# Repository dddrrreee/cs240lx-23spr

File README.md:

## CS240lx: advanced operating system lab, accelerated
### Engler, Spr 2023.

tl;dr index:

  - [This is a lab class and here are the labs](./labs/).
  - [Course website](https://github.com/dddrrreee/cs240lx-23spr).
  - [Course newsgroup](https://github.com/dddrrreee/cs240lx-23spr).
  - To get the repository: 

        git clone git@github.com:dddrrreee/cs240lx-23spr.git

    Put the path to the repo in your shell startup file:

    E.g. for `tcsh` I put the following in my `.tcshrc` file (and
    did `source ~/.tcshrc` after):
 
        setenv CS240LX_2023_PATH /home/engler/class/cs240lx-23spr/

    If these steps worked, you should be able to type `make` and have
    it work.

This is a implementation-heavy, lab-based class that will cover similar
topics as CS240 --- threads, virtual memory, file systems and distributed
systems --- but by writing code versus discussing papers.  After taking an
initial operating systems course you are often left in the odd situation
of having spent significant time getting the background knowledge needed
to do interesting actions, but not being left with enough time to actually
do them.  This course attacks this problem by assuming basic knowledge and
using it as a springboard to advance quickly through a set of powerful,
useful techniques that even advanced practioners can be ignorant of.

We will write custom code from scratch for the widely-used, ARM-based
raspberry pi; our code will run "bare-metal" without an operating system,
which means we can do interesting things without constantly fighting
with a lumbering OS that cannot get out of its own way.

By combining research insights (many unpublished) and our our lightweight
bare-metal code we will be in the unusual position of having foundational
abilities that most people have assumed are in-practice impossible.
As one example, we will implement fast, flexible exception handling
and then use this ability to build a variety of tools that find race
conditions, check code correctness, and memory  corruption.  By using
exceptions rather than binary rewriting we can build tools that find
similar errors as Purify / Valgrind, but can be implemented in merely
hundreds rather than hundreds of thousands of lines of code; our tools
will also be faster and more extensible.

Our initial plan was to do ten projects, one per week, where each project
covers two labs of (at a minimum) several hours each and a non-trivial
amount of outside work.

The course workload is significant, but I will aim to not waste your time.
CS140E is strongly encouraged as a prerequisite, but a sufficiently
talented and motivated implementor can make up for its lack.

I'm teaching this course because doing CS140E was was so much fun.
Each time I drove into lab, I would get an idea for one or two additional
labs I really wanted to do, and each time I wrote up an lab there would
be a long `NOTES.txt` of additional ideas.  After last year and this, I
have a big document of all the possible ideas.  This class will implement
the ones that seem the most interesting.

Staff:
  - head TA: Matthew Sotoudeh [email is last name]
  - Dawson Engler.

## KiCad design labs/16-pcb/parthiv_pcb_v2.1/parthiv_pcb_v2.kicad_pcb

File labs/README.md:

## 240lx Labs.

This is a partial set of tentative labs.  They've been split into
ones we'll almost certainly do and those that we might do depending
on interest.  In either case, they will change!  Some will get dropped.
Some will get added.  All will get modified significantly.

[Last year's repo has a ton of
labs](https://github.com/dddrrreee/cs240lx-22spr/tree/main/labs)
if you look through the subdirectories.  It's worth going through these
and letting us know which seem most interesting.

   - There are way more possible labs than class slots so if you can
     please look through these after the first class and see which
     you prefer.

This is the third offering of the class.  While we have done many of
the labs once before in cs240lx or cs340lx many ideas are research-paper
level and how to best implement them is still up in the air, so the only
constant will be change.

Currently looking at roughly ten projects, two labs per project.
Some rough grouping of projects:

  1. Low level hacks. A set of projects that do low level code hacking

     - [1-dynamic-code-gen](1-dynamic-code-gen/README.md): you'll learn
       how to generate executable machine code at runtime and how to 
       use this trick to do neat stuff.  

     - Fast code. Expose and use the many armv1176 performance counters
       to make code as fast and low error as possible.  Seeing what
       causes TLB misses, cache misses, branch misses, cycles, etc really
       clarifies how the machine works.

     - Timing accurate code: Build a digital analyzer. The pi is fast
       enough, and flexible enough that we can easily build a logic
       analyzer that (as far as I can tell) is faster --- and certainly
       more flexible --- then commercial logic analyzers that cost
       hundreds of dollars.  You'll learn how to write consistently
       nanosecond accurate code.

       The digital analyzer can be viewed as a way to do `printf`
       for devices.  We'll use it to reverse engineer the SPI, I2C and
       UART protocols.  We'll also make it so you can upload code into
       it to do more interesting checks (e.g., that real time threads hit
       their schedules).

       A big challenge is getting the error / variance from one sample to
       another --- you'll use both memory protection tricks and interrupts
       to shrink the monitoring loop down far enough that it runs with an
       order of a few nanosecond error.

  2. Tools using debugging hardware.   We'll use the pi debug hardware
     to write simple versions of useful tools that either require 
     millions of lines of code using other approaches or in fact have 
     never been built.

     - [Trap-based Eraser]: Eraser is a famous race detection tool that
       uses binary-rewriting to instrumenting every load and store and
       flagging if a thread accessed the memory with inconsistent set of
       locks (its *lockset*).  Doing binary rewriting is hard.  By using
       debugging hardware and fast traps we can build a version in a few
       hundred lines of code: simply trap on every load and store and
       implement the lockset algorithm.
     
     - [Trap-based memory checking]: Valgrind dynamically rewrites binaries
       so that it can instruments every load and store.  Dynamically
       rewriting binary is harder in some ways than the static rewriting
       that Eraser does, which was already really hard.  You will use your
       traps to implement a much simpler method:
   
          - Mark all heap memory as unavailable.
          - In the trap handler, determine if the faulting address is in bounds.
          - If so: do the load or store and return.
          - If not: give an error.
      
       Given how fast our traps are, and how slow valgrind is, your approach
       may actually be faster.
      
       To get around the need for *referents* (that track which block of
       memory a pointer is supposed to point to) you'll use randomized
       allocation and multiple runs.

     - [Thorough conconcurrency checking]: we will use traps to build a simple,
       very thorough lock-free checking tool.  Given a lock free algorithm and
       two threads:

        - Mark its memory as inaccessible.
        - On each resulting fault, do the instruction but then context switch
          to another thread.
        - At the end, record the result.
        - Then rerun the thread code from a clean initial state without doing
          context switches.   For the type of code we run: Any difference
          is an error.

       To be really fancy, we can buffer up the stores that are done and
       then try all possible legal orders of them when the other thread
       does a load.  This checker should find a lot of bugs.

       To speed up checking we use state hashing to prune out redundant
       states: at each program counter value, hash all previous stores,
       if we get the same hash as before, we know we will compute the same
       results as a previous and can stop exploring.

     - [Possible: Volatile cross-checking] A common, nasty problem in
       embedded code is that programs code use raw pointers to manipulate
       device memory, but either the programmer does not use `volatile`
       correctly or the compiler has a bug.  We can detect such things with
       a simple hack:

       - We know that device references should remain the same no matter
         how the code is compiled.
       - So compile a piece of code multiple ways: with no optimization, `-O`,
       `-O2`, with fancier flags, etc.
       - Then run each different version, using ARM domain tricks to trace
         all address / values that are read and written.
       - Compare these: any difference signals a bug.
 
       This tool would have caught many errors we made when designing cs107e;
       some of them took days to track down.

   3. Device code.  140e was packed enough that we didn't' do many devices,
      which are where alot of the fun is.  We'll do a bunch of fun 
      devices across the quarter.

      Writing drivers from scratch gives a better feel for hardware.
      Device driver code makes up 90+% of OS code, so it makes sense to
      learn how to write this kind of code.   We'll likely do some amount
      of building a fake-pi implementation to check this code.

      - ws2812b: you'll write nanosecond accurate
        code to control a WS2812B light string.  The WS2812B is
        fairly common, fairly cheap.  Each pixel has 8-bits of color
        (red-green-blue) and you can turn on individual lights in
        the array.

      - [i2c-driver](i2c-driver/README.md): You'll use the broadcom
        document to write your own I2C implementation from scratch (no helper
        code) and delete ours.

        To help testing, you'll also write a driver for the popular ADS1115
        analog-to-digital converter (also from scratch).  Analog devices
        (that output a varying voltage) are typically the cheapest ones.
        Unfortunately your r/pi cannot take their input directly.  We will
        use your I2C driver to read inputs from a microphone and control
        the light array with it.

      - [spi-driver]: SPI is a common, simple protocol.  You'll implement
        it and use it to control a digital-to-analogue converter and to
        control an OLED screen.

      - A sound reactive equalizer: you'll use the ws2812b light strips
        and an I2S microphone to decode audio into frequencies and 
        display the results.  It's pretty, and pretty fun.

      - A movement reactive equalizer: you'll use the ws2812b light strips
        and an accelerometer decode movement into patterns and
        display the results.  It's pretty, and pretty fun.  Part of this
        will use a network bootloader.

   4. OS hacking.

      - Network bootloader.  One big thing missing was having a network
        bootloader so we could control multiple pi's easily.  We'll also
        write a simple, reliable FIFO protocol so we can control  the
        systems.

      - Other chips.  We've written code on the r/pi A+, which is
        fine. One thing I would love to get out of this class is having
        the first set of 140E labs ported to a bunch of other chips.
        The tentative plan is to port to a risc-v and potentially the pi
        pico chip, and get the initial 140e labs running with a version
        of our bootloader.

      - A clean FAT32 read/write implementation.

      - Some other OS stuff!  Ideally a simple distributed OS.
        
   5. Possible: PCB design.  I'm hoping we can do a simple PCB version
      using Parthiv's kicad lab from 340lx.

---------------------------------------------------------------------
Possibles:
  - In cs340lx we spun up some hifive2 riscv boards and then wrote a simple
    simulator that could run itself.  I later used this to make a symbolic
    execution engine with a few hundred lines of code.  Using riscv is a
    great method for doing binary analysis since its  a much simpler system
    than ARM or valgrind intermediate representation.  We'll do several labs
    building this.

  - have you write a simple static bug
    finding system based on "micro-grammars", a trick we came up with
    that does incomplete parsing of languages (so the parser is small
    --- a few hundred lines versus a million) but does it well enough
    that you can find many clean bugs with few false positives. It'd be
    fantastic if you guys could write your own system and go out and find
    a bunch of real bugs in the large systems you'll be dealing with.
    The main limit is me finding a few days to build this out and try
    to break it down in a way that doesn't require compiler background
    (this is feasible, I am just badly managing time).

  - Make a simple distributed system.  One use case is doing crypto
    mining on a linked set of r/pi chips.

  - As a way to help testing (among other things): do a real writeable
    file system so that we can save the binaries to run, the output,
    etc and use scripting (via FUSE) to easily interact with your pi
    through your normal shell.  We could also use the RF chip to make
    this distributed.

  - More speculatively: do very sleazy symbolic execution  to generate
    inputs to run code on (and, e.g., find differences in today's code
    versus yesterday's) by inferring what each machine instruction does by
    running it in its own address space, seeing how the registers change,
    how memory is read and written, and then matching this against known
    micro-ops (or compositions of them).  You can then use this to run
    the binary to get constraints and then use a constraint solver to
    solve them and rerun the result on the code.  If we can do this it
    will be a very powerful trick, since its simple enough to work in
    real life (unlike the current symbolic systems).

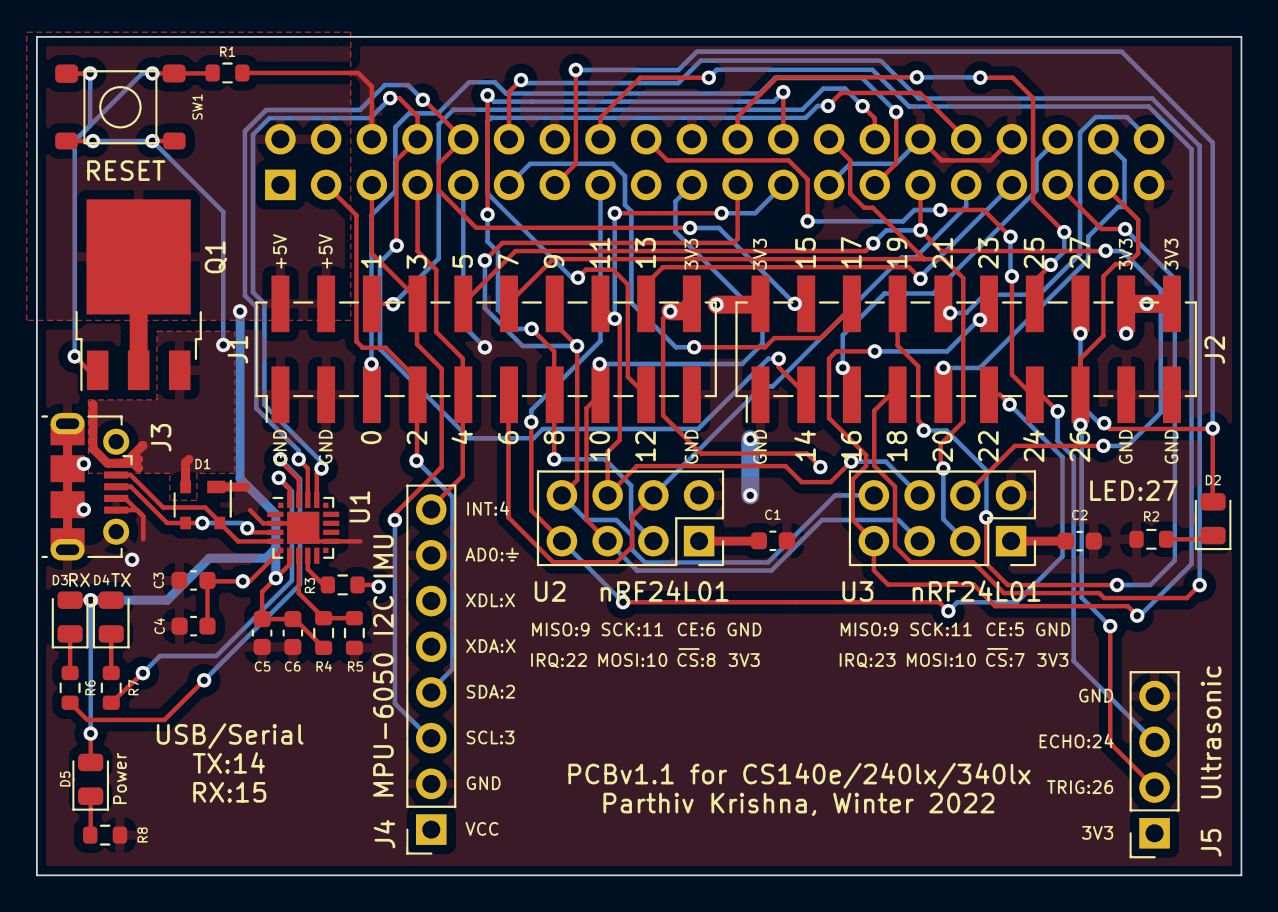
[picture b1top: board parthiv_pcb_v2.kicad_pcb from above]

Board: 2 copper layers, 66.9 x 46.6 mm, 30 parts (1 on the bottom side), 43 nets.

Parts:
C1, C2: 10uF; C_0603_1608Metric
C3, C5: 4.7uF; C_0603_1608Metric
C4, C6: 100nF; C_0603_1608Metric
D1: SP0503BAHT; SOT-143
D2, D3, D4, D5: LED; LED_0805_2012Metric
J1, J2: Conn_02x10_Odd_Even; PinHeader_2x10_P2.54mm_Vertical_SMD
J3: USB_B_Micro; USB_Micro-B_Molex-105017-0001
J4: MPU6050; PinSocket_1x08_P2.54mm_Vertical
J5: Ultrasonic; PinSocket_1x04_P2.54mm_Vertical
J6: Raspberry_Pi_2_3; PinSocket_2x20_P2.54mm_Vertical
Q1: Q_PMOS_GDS; TO-252-3_TabPin2
R1: 10k; R_0603_1608Metric
R2: 100; R_0603_1608Metric
R3, R6, R7, R8: 1k; R_0603_1608Metric
R4: 22k; R_0603_1608Metric
R5: 47k; R_0603_1608Metric
SW1: RESET; Button_TS-1187A-B-A-B
U1: CP2102N-Axx-xQFN20; SiliconLabs_QFN-20-1EP_3x3mm_P0.5mm_EP1.8x1.8mm
U2, U3: NRF24L01; PinSocket_2x04_P2.54mm_Vertical

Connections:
+3V3: C1.1, C2.1, C3.1, C4.1, J1.20, J2.2, J2.18, J2.20, J4.1 (VCC), J5.1 (VCC), J6.1 (3V3), J6.17 (3V3), R3.1, U1.6 (VDD), U2.1 (VCC), U3.1 (VCC)
+5V: C5.1, C6.1, D3.2 (A), D4.2 (A), D5.2 (A), J1.2, J1.4, J6.2 (5V), J6.4 (5V), Q1.2 (D), R4.1, U1.7 (VREGIN)
/CP2102N/USBD+: D1.3 (K), J3.3 (D+), U1.4 (D+)
/CP2102N/USBD-: D1.4 (K), J3.2 (D-), U1.5 (D-)
/CP2102N/VBUS_DIV: R4.2, R5.1, U1.8 (VBUS)
/CP2102N/nRESET: Q1.1 (G), R1.1, SW1.1
/CP2102N/nRXLED: R6.2, U1.19 (~RXT/GPIO.3)
/CP2102N/nTXLED: R7.2, U1.20 (~TXT/GPIO.2)
GND: C1.2, C2.2, C3.2, C4.2, C5.2, C6.2, D1.1 (A), J1.1, J1.3, J1.19, J2.1, J2.17, J2.19, J3.4 (ID), J3.5 (GND), J3.6 (Shield), J4.2 (GND), J4.7 (AD0), J5.4 (GND), J6.6 (GND), J6.9 (GND), J6.14 (GND), J6.20 (GND), J6.25 (GND), J6.30 (GND), J6.34 (GND), J6.39 (GND), R1.2, R2.2, R5.2, R8.2, U1.3 (GND), U1.12 (GND), U1.21 (GND), U2.2 (GND), U3.2 (GND)
GPIO0: J1.5, J6.27 (ID_SD/GPIO0)
GPIO1: J1.6, J6.28 (ID_SC/GPIO1)
GPIO2: J1.7, J4.4 (SDA), J6.3 (SDA/GPIO2)
GPIO3: J1.8, J4.3 (SCL), J6.5 (SCL/GPIO3)
GPIO4: J1.9, J4.8 (INT), J6.7 (GCLK0/GPIO4)
GPIO5: J1.10, J6.29 (GCLK1/GPIO5), U3.4 (CE)
GPIO6: J1.11, J6.31 (GCLK2/GPIO6), U2.4 (CE)
GPIO7: J1.12, J6.26 (~CE1/GPIO7), U3.3 (~CSN)
GPIO8: J1.13, J6.24 (~CE0/GPIO8), U2.3 (~CSN)
GPIO9: J1.14, J6.21 (MISO0/GPIO9), U2.8 (MISO), U3.8 (MISO)
GPIO10: J1.15, J6.19 (MOSI0/GPIO10), U2.5 (MOSI), U3.5 (MOSI)
GPIO11: J1.16, J6.23 (SCLK0/GPIO11), U2.6 (SCK), U3.6 (SCK)
GPIO12: J1.17, J6.32 (PWM0/GPIO12)
GPIO13: J1.18, J6.33 (PWM1/GPIO13)
GPIO14: J2.3, J6.8 (GPIO14/TXD), U1.17 (RXD)
GPIO15: J2.4, J6.10 (GPIO15/RXD), U1.18 (TXD)
GPIO16: J2.5, J6.36 (GPIO16)
GPIO17: J2.6, J6.11 (GPIO17)
GPIO18: J2.7, J6.12 (GPIO18/PWM0)
GPIO19: J2.8, J6.35 (GPIO19/MISO1)
GPIO20: J2.9, J6.38 (GPIO20/MOSI1)
GPIO21: J2.10, J6.40 (GPIO21/SCLK1)
GPIO22: J2.11, J6.15 (GPIO22), U2.7 (IRQ)
GPIO23: J2.12, J6.16 (GPIO23), U3.7 (IRQ)
GPIO24: J2.13, J5.3 (ECHO), J6.18 (GPIO24)
GPIO25: J2.14, J6.22 (GPIO25)
GPIO26: J2.15, J5.2 (TRIG), J6.37 (GPIO26)
GPIO27: D2.2 (A), J2.16, J6.13 (GPIO27)
unnamed: D2.1 (K), R2.1
unnamed: D3.1 (K), R6.1
unnamed: D4.1 (K), R7.1
unnamed: D5.1 (K), R8.1
unnamed: R3.2, U1.9 (~RST)
VBUS: D1.2 (K), J3.1 (VBUS), Q1.3 (S), SW1.2

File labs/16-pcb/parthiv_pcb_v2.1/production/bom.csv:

Designator,Footprint,Quantity,Value,LCSC Part #
"C1, C2",C_0603_1608Metric,2,10uF,C96446
"C3, C5",C_0603_1608Metric,2,4.7uF,C19666
"C4, C6",C_0603_1608Metric,2,100nF,C14663
"D1, D3, D4, D5",LED_0805_2012Metric,4,LED,C440522
D2,SOT-143,1,SP0503BAHT,C3029025
J1,PinHeader_2x20_P2.54mm_Vertical_SMD,1,Conn_02x20_Odd_Even,C2685181
J2,USB_Micro-B_Molex-105017-0001,1,USB_B_Micro,C381143
J3,PinSocket_1x06_P2.54mm_Vertical,1,Adafruit_I2S_Mic,C2935900
J4,PinSocket_1x08_P2.54mm_Vertical,1,MPU6050,C2935979
J5,PinSocket_2x20_P2.54mm_Vertical,1,Raspberry_Pi_2_3,C132132
Q1,TO-252-3_TabPin2,1,Q_PMOS_GDS,C326372
R1,R_0603_1608Metric,1,10k,C25804
R2,R_0603_1608Metric,1,100,C22775
"R3, R6, R7, R8",R_0603_1608Metric,4,1k,C21190
R4,R_0603_1608Metric,1,22k,C31850
R5,R_0603_1608Metric,1,47k,C25819
SW1,Button_TS-1187A-B-A-B,1,RESET,C318884
U1,SiliconLabs_QFN-20-1EP_3x3mm_P0.5mm_EP1.8x1.8mm,1,CP2102N-Axx-xQFN20,C969913
"U2, U3",PinSocket_2x04_P2.54mm_Vertical,2,NRF24L01,C2935984

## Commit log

2023-04-04 minor
2023-04-06 mailxo
2023-04-12 dfdd
2023-04-13 new lab
2023-04-19 added 4
2023-04-19 more
2023-04-20 last minute gc lab
2023-04-25 added
2023-04-28 stuff
2023-04-28 added float
2023-05-03 neopix
2023-05-10 Add prelab
2023-05-10 verilog handout code
2023-05-10 Add script
2023-05-10 chmod
2023-05-10 unquarantine update
2023-05-10 update instructions
2023-05-10 ignore
2023-05-11 initial
2023-05-11 useful pdfs
2023-05-11 useful images
2023-05-16 renamed to lab 12.
2023-05-17 2023 path
2023-05-17 uart lab
2023-05-18 Add verilator.txt
2023-05-19 Add screen to makefile tx
2023-05-19 fix starter
2023-05-30 parthiv's pcb lab
2023-05-31 more prose
2023-05-31 add visit trace
2023-05-31 bugfix
2023-05-31 fixing
2023-05-31 seems fixed now
2023-05-31 ignore swaps
2023-05-31 expl
2023-05-31 clarify
2023-05-31 add staff output for lexer
2023-05-31 copy prose to README
2023-05-31 add a main function for the compiler
2023-05-31 helper scripts & utils
2023-05-31 some extensions
2023-06-02 all target for makefile
2023-06-02 fix check repo script
